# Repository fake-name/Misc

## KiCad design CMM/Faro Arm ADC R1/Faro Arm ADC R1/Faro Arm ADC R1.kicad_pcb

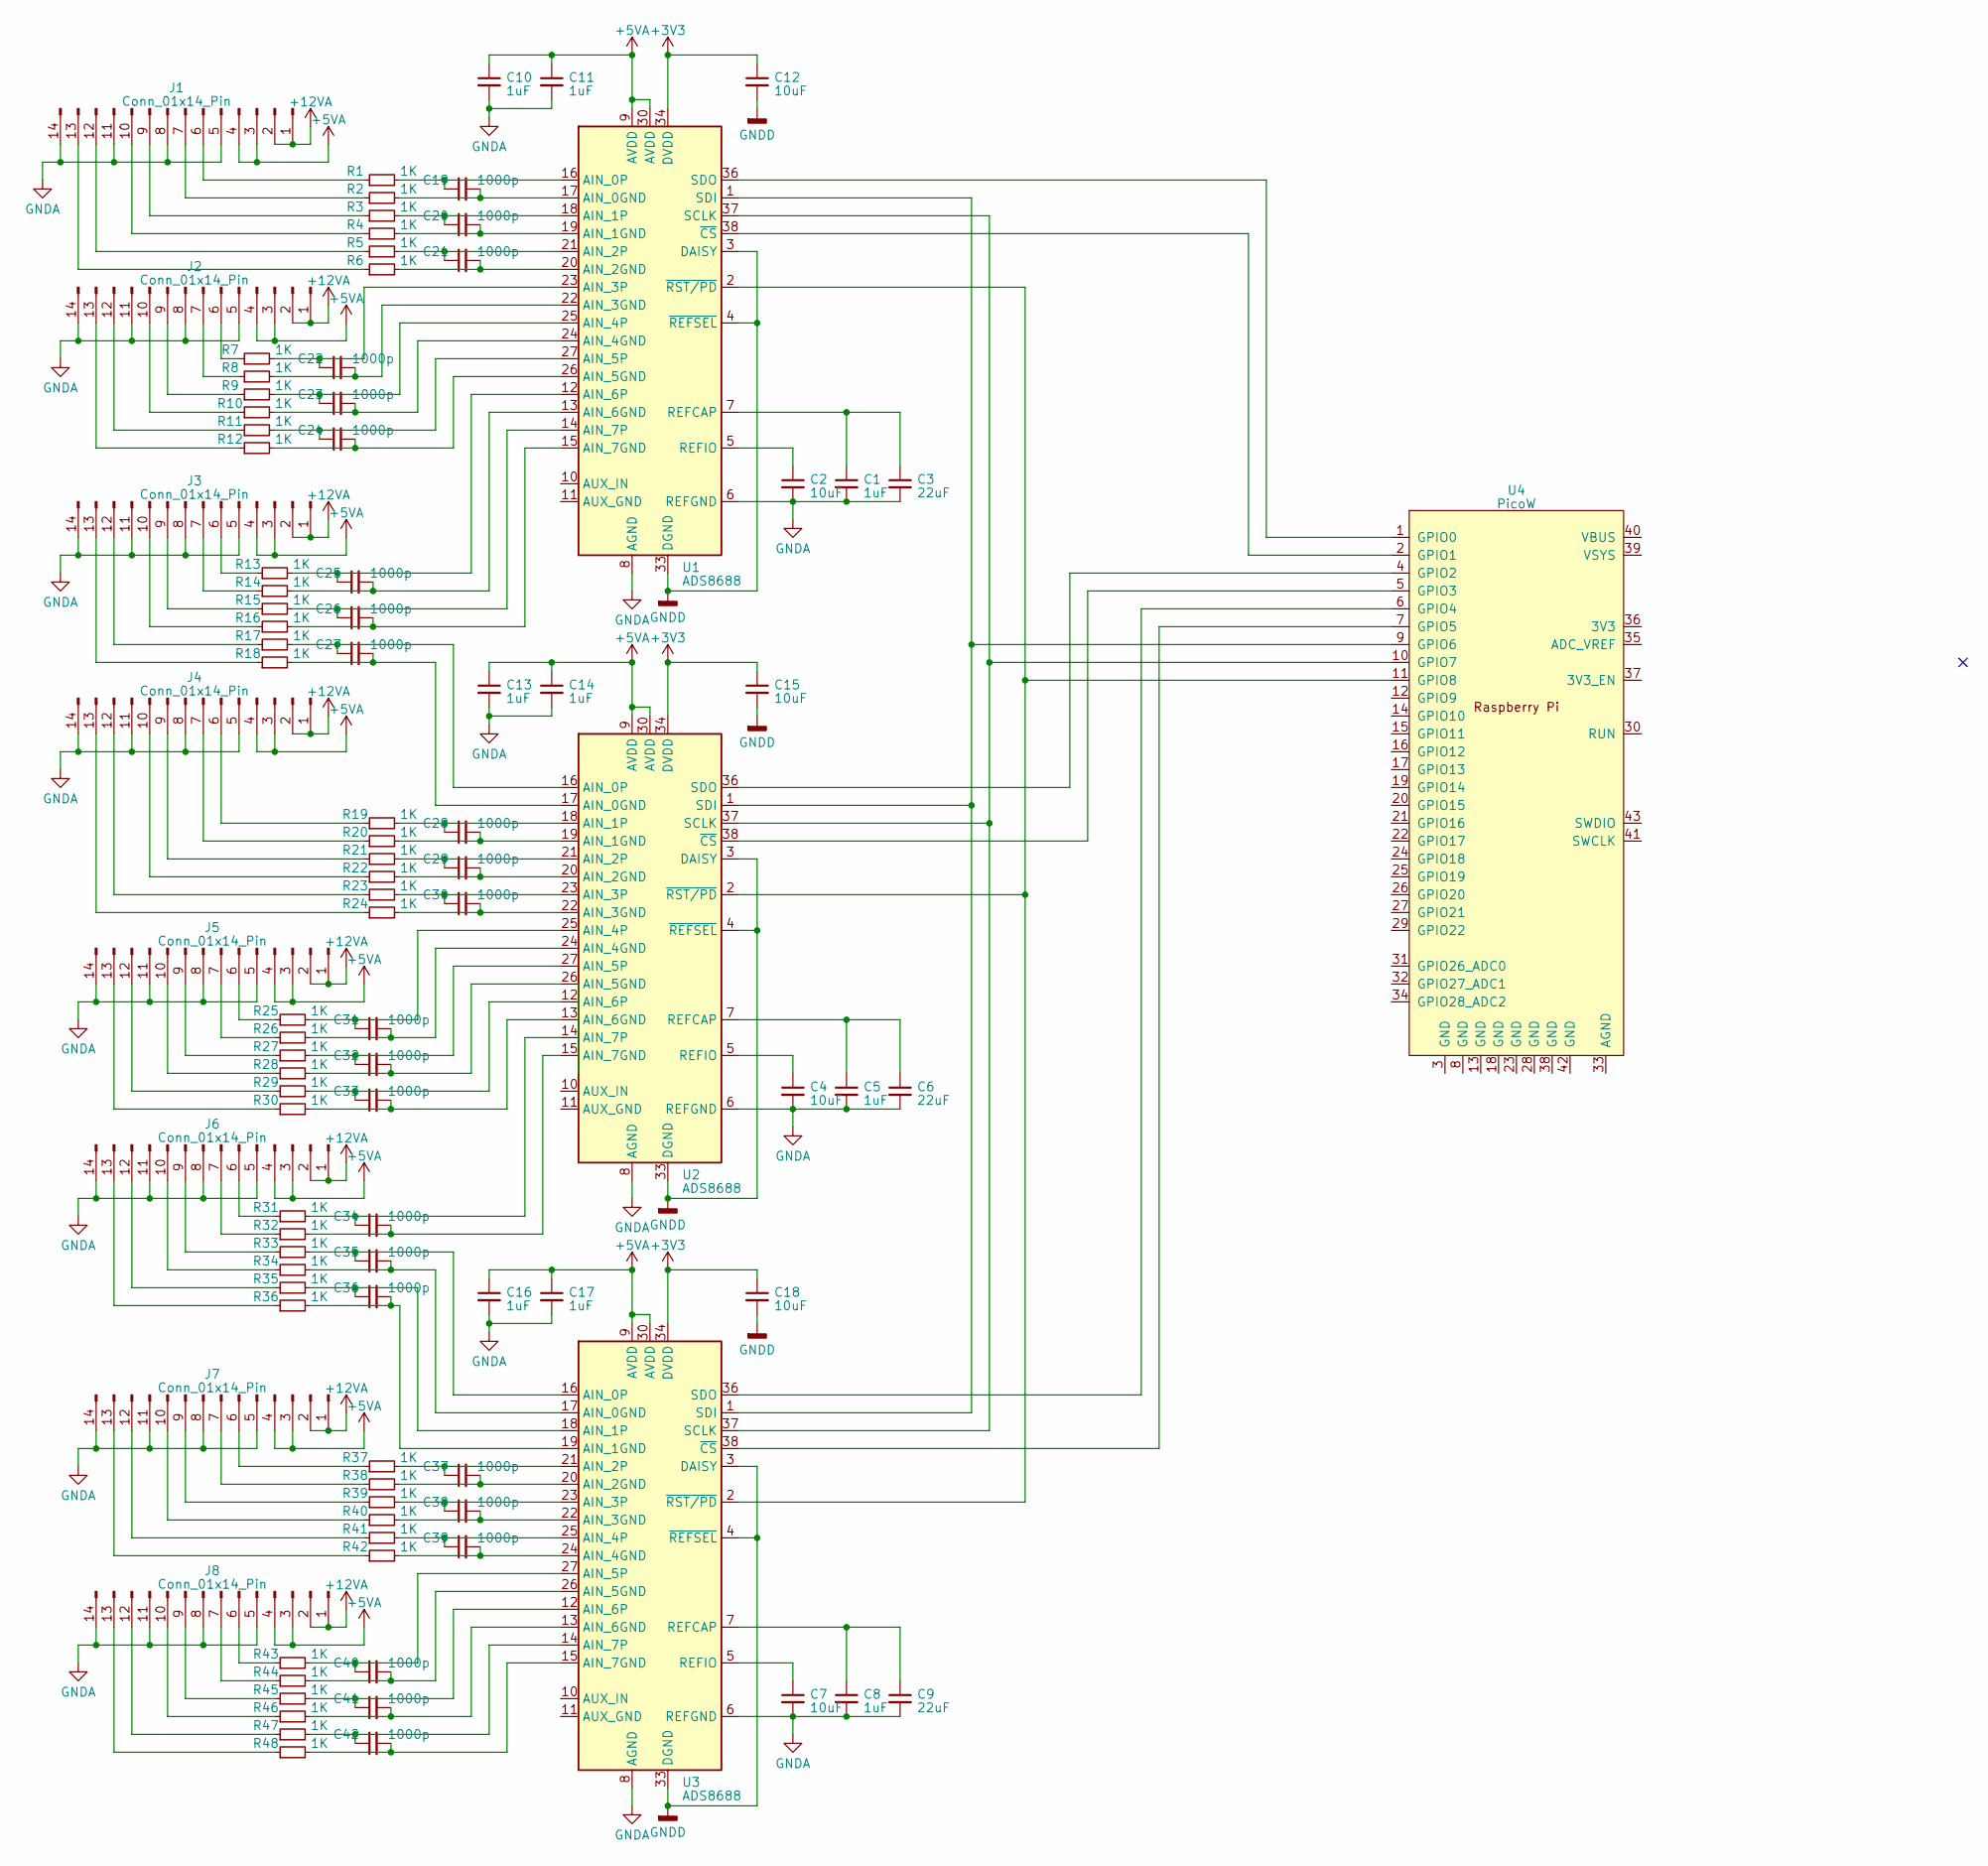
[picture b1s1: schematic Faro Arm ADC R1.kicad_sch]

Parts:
C1, C5, C8, C10, C11, C13, C14, C16, C17: 1uF; C_0603_1608Metric
C2, C4, C7, C12, C15, C18: 10uF; C_0805_2012Metric
C3, C6, C9: 22uF; C_0805_2012Metric
C19, C20, C21, C22, C23, C24, C25, C26, C27, C28, C29, C30, C31, C32, C33, C34, C35, C36, C37, C38, C39, C40, C41, C42: 1000p; C_0603_1608Metric
J1, J2, J3, J4, J5, J6, J7, J8: Conn_01x14_Pin; IDC-Header_2x07_P2.54mm_Vertical
R1, R2, R3, R4, R5, R6, R7, R8, R9, R10, R11, R12, R13, R14, R15, R16, R17, R18, R19, R20, R21, R22, R23, R24, R25, R26, R27, R28, R29, R30, R31, R32, R33, R34, R35, R36, R37, R38, R39, R40, R41, R42, R43, R44, R45, R46, R47, R48: 1K; R_0603_1608Metric
U1, U2, U3: ADS8688; TSSOP-38_4.4x9.7mm_P0.5mm
U4: PicoW; RPi_PicoW_SMD_TH

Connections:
+3V3: C12.1, C15.1, C18.1, U1.34 (DVDD), U2.34 (DVDD), U3.34 (DVDD)
GNDA: C1.2, C2.2, C3.2, C4.2, C5.2, C6.2, C7.2, C8.2, C9.2, C10.2, C11.2, C13.2, C14.2, C16.2, C17.2, J1.5, J1.8, J1.11, J1.14, J2.5, J2.8, J2.11, J2.14, J3.5, J3.8, J3.11, J3.14, J4.5, J4.8, J4.11, J4.14, J5.5, J5.8, J5.11, J5.14, J6.5, J6.8, J6.11, J6.14, J7.5, J7.8, J7.11, J7.14, J8.5, J8.8, J8.11, J8.14, U1.6 (REFGND), U1.8 (AGND), U1.28 (AGND), U1.29 (AGND), U1.31 (AGND), U1.32 (AGND), U2.6 (REFGND), U2.8 (AGND), U2.28 (AGND), U2.29 (AGND), U2.31 (AGND), U2.32 (AGND), U3.6 (REFGND), U3.8 (AGND), U3.28 (AGND), U3.29 (AGND), U3.31 (AGND), U3.32 (AGND)
GNDD: C12.2, C15.2, C18.2, U1.3 (DAISY), U1.4 (~REFSEL), U1.33 (DGND), U2.3 (DAISY), U2.4 (~REFSEL), U2.33 (DGND), U3.3 (DAISY), U3.4 (~REFSEL), U3.33 (DGND)
unnamed: J1.6, R1.1
unnamed: J1.7, R2.1
unnamed: J1.9, R3.1
unnamed: J1.10, R4.1
unnamed: J1.12, R5.1
unnamed: J1.13, R6.1
unnamed: J2.6, R7.1
unnamed: J2.7, R8.1
unnamed: J2.9, R9.1
unnamed: J2.10, R10.1
unnamed: J2.12, R11.1
unnamed: J2.13, R12.1
unnamed: J3.6, R13.1
unnamed: J3.7, R14.1
unnamed: J3.9, R15.1
unnamed: J3.10, R16.1
unnamed: J3.12, R17.1
unnamed: J3.13, R18.1
unnamed: J4.6, R19.1
unnamed: J4.7, R20.1
unnamed: J4.9, R21.1
unnamed: J4.10, R22.1
unnamed: J4.12, R23.1
unnamed: J4.13, R24.1
unnamed: J5.6, R25.1
unnamed: J5.7, R26.1
unnamed: J5.9, R27.1
unnamed: J5.10, R28.1
unnamed: J5.12, R29.1
unnamed: J5.13, R30.1
unnamed: J6.6, R31.1
unnamed: J6.7, R32.1
unnamed: J6.9, R33.1
unnamed: J6.10, R34.1
unnamed: J6.12, R35.1
unnamed: J6.13, R36.1
unnamed: J7.6, R37.1
unnamed: J7.7, R38.1
unnamed: J7.9, R39.1
unnamed: J7.10, R40.1
unnamed: J7.12, R41.1
unnamed: J7.13, R42.1
unnamed: J8.6, R43.1
unnamed: J8.7, R44.1
unnamed: J8.9, R45.1
unnamed: J8.10, R46.1
unnamed: J8.12, R47.1
unnamed: J8.13, R48.1
unnamed: C19.2, R2.2, U1.17 (AIN_0GND)
unnamed: C19.1, R1.2, U1.16 (AIN_0P)
unnamed: C20.2, R4.2, U1.19 (AIN_1GND)
unnamed: C20.1, R3.2, U1.18 (AIN_1P)
unnamed: C21.2, R6.2, U1.20 (AIN_2GND)
unnamed: C21.1, R5.2, U1.21 (AIN_2P)
unnamed: C22.2, R8.2, U1.22 (AIN_3GND)
unnamed: C22.1, R7.2, U1.23 (AIN_3P)
unnamed: C23.2, R10.2, U1.24 (AIN_4GND)
unnamed: C23.1, R9.2, U1.25 (AIN_4P)
unnamed: C24.2, R12.2, U1.26 (AIN_5GND)
unnamed: C24.1, R11.2, U1.27 (AIN_5P)
unnamed: C25.2, R14.2, U1.13 (AIN_6GND)
unnamed: C25.1, R13.2, U1.12 (AIN_6P)
unnamed: C26.2, R16.2, U1.15 (AIN_7GND)
unnamed: C26.1, R15.2, U1.14 (AIN_7P)
unnamed: C1.1, C3.1, U1.7 (REFCAP)
unnamed: C2.1, U1.5 (REFIO)
unnamed: U1.37 (SCLK), U2.37 (SCLK), U3.37 (SCLK), U4.10 (GPIO7)
unnamed: U1.1 (SDI), U2.1 (SDI), U3.1 (SDI), U4.9 (GPIO6)
unnamed: U1.36 (SDO), U4.1 (GPIO0)
unnamed: U1.38 (~CS), U4.2 (GPIO1)
unnamed: U1.2 (~RST/PD), U2.2 (~RST/PD), U3.2 (~RST/PD), U4.11 (GPIO8)
unnamed: C27.2, R18.2, U2.17 (AIN_0GND)
unnamed: C27.1, R17.2, U2.16 (AIN_0P)
unnamed: C28.2, R20.2, U2.19 (AIN_1GND)
unnamed: C28.1, R19.2, U2.18 (AIN_1P)
unnamed: C29.2, R22.2, U2.20 (AIN_2GND)
unnamed: C29.1, R21.2, U2.21 (AIN_2P)
unnamed: C30.2, R24.2, U2.22 (AIN_3GND)
unnamed: C30.1, R23.2, U2.23 (AIN_3P)
unnamed: C31.2, R26.2, U2.24 (AIN_4GND)
unnamed: C31.1, R25.2, U2.25 (AIN_4P)
unnamed: C32.2, R28.2, U2.26 (AIN_5GND)
unnamed: C32.1, R27.2, U2.27 (AIN_5P)
unnamed: C33.2, R30.2, U2.13 (AIN_6GND)
unnamed: C33.1, R29.2, U2.12 (AIN_6P)
unnamed: C34.2, R32.2, U2.15 (AIN_7GND)
unnamed: C34.1, R31.2, U2.14 (AIN_7P)
unnamed: C5.1, C6.1, U2.7 (REFCAP)
unnamed: C4.1, U2.5 (REFIO)
unnamed: U2.36 (SDO), U4.4 (GPIO2)
unnamed: U2.38 (~CS), U4.5 (GPIO3)
unnamed: C35.2, R34.2, U3.17 (AIN_0GND)
unnamed: C35.1, R33.2, U3.16 (AIN_0P)
unnamed: C36.2, R36.2, U3.19 (AIN_1GND)
unnamed: C36.1, R35.2, U3.18 (AIN_1P)
unnamed: C37.2, R38.2, U3.20 (AIN_2GND)
unnamed: C37.1, R37.2, U3.21 (AIN_2P)
unnamed: C38.2, R40.2, U3.22 (AIN_3GND)
unnamed: C38.1, R39.2, U3.23 (AIN_3P)
unnamed: C39.2, R42.2, U3.24 (AIN_4GND)
unnamed: C39.1, R41.2, U3.25 (AIN_4P)
unnamed: C40.2, R44.2, U3.26 (AIN_5GND)
unnamed: C40.1, R43.2, U3.27 (AIN_5P)
unnamed: C41.2, R46.2, U3.13 (AIN_6GND)
unnamed: C41.1, R45.2, U3.12 (AIN_6P)
unnamed: C42.2, R48.2, U3.15 (AIN_7GND)
unnamed: C42.1, R47.2, U3.14 (AIN_7P)
unnamed: C8.1, C9.1, U3.7 (REFCAP)
unnamed: C7.1, U3.5 (REFIO)
unnamed: U3.36 (SDO), U4.6 (GPIO4)
unnamed: U3.38 (~CS), U4.7 (GPIO5)

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
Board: 2 copper layers, 102 parts (0 on the bottom side), 115 nets, no tracks yet.

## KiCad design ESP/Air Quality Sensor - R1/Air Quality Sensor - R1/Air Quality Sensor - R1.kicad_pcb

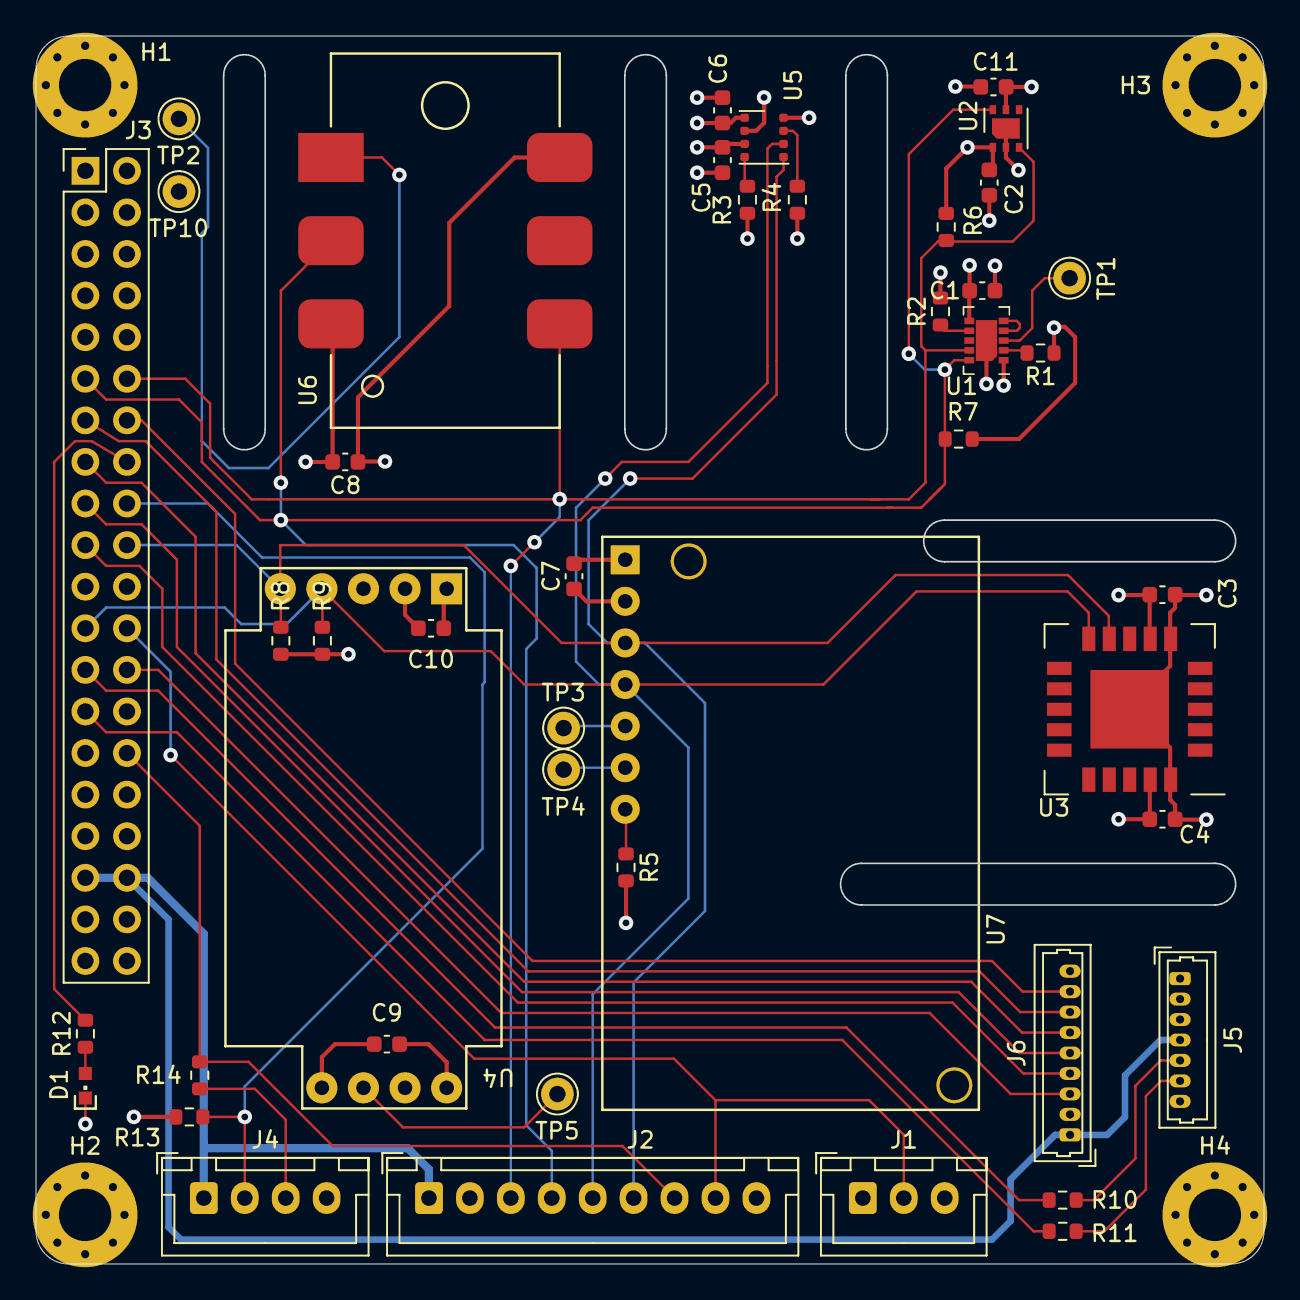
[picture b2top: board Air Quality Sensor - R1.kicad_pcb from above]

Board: 4 copper layers, 75.0 x 75.0 mm, 49 parts (0 on the bottom side), 34 nets.

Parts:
C1, C3, C4, C5, C6, C8, C9, C10, C11: 0.1u; C_0603_1608Metric
C2, C7: 1.0u; C_0603_1608Metric
D1: LED; CHIPLED_0603
H1, H2, H3, H4: MountingHole; MountingHole_3.2mm_M3_Pad_Via
J1: Conn_01x05; JST_XH_B3B-XH-A_1x03_P2.50mm_Vertical
J2: Conn_01x09; JST_XH_B9B-XH-A_1x09_P2.50mm_Vertical
J3: ESP32-DevBoard-Header; PinHeader_2x20_P2.54mm_Vertical
J4: Conn_01x04; JST_XH_B4B-XH-A_1x04_P2.50mm_Vertical
J5: Conn_01x09; Molex_PicoBlade_53047-0710_1x07_P1.25mm_Vertical
J6: Conn_01x08; Molex_PicoBlade_53047-0910_1x09_P1.25mm_Vertical
R1, R3, R4, R5, R6, R7, R8, R9, R10, R11, R13: 4.7K; R_0603_1608Metric
R2: 47K; R_0603_1608Metric
R12, R14: 470R; R_0603_1608Metric
TP1, TP2, TP3, TP4, TP5, TP10: TestPoint_Small; Pin_D1.0mm_L10.0mm
U1: CCS811; AMS_LGA-10-1EP_2.7x4mm_P0.6mm
U2: SGP40; Sensirion_DFN-6-1EP_2.44x2.44mm_P0.8mm
U3: SCD4X; Sensirion_SCD4X_QFN-20_EP_10.1x10.1_Pitch1.25mm
U4: Sensair_Sunrise_006-0-0007
U5: BME680; Bosch_LGA-8_3x3mm_P0.8mm_ClockwisePinNumbering
U6: MICS-VZ-89TE‎; Telaire_MICS-VZ-89TE‎
U7: SCD30; Sensiron_SCD30_Module

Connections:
+3V3: C1.1, C2.1, C3.1, C4.1, C5.1, C6.1, C7.1, C8.1, C9.1, C10.1, C11.1, J1.1, J2.2, J3.3 (3V3), J3.4 (3V3), J3.33 (3V3), J3.34 (3V3), J6.2, R1.1, R3.1, R4.1, R6.2, R7.2, R8.2, R9.2, R13.2, U1.6 (VDD), U2.1 (VDD), U2.5 (VDDH), U3.7 (VDD), U3.19 (VDDH), U4.2 (VBB), U4.3 (VDDIO), U4.9 (EN), U5.6 (VDDIO), U5.8 (VDD), U6.6 (3.3V), U7.1 (VDD)
+5V: J2.1, J3.35 (5V0), J3.36 (5V0), J4.1, J5.4, J6.1
/SENS/SCL_1: J2.6, J3.20 (IO22), R8.1, U3.9 (SCL), U4.5 (TxD/SCL), U5.4 (SCK), U7.3 (TX/SCL)
/SENS/SCL_2: J2.4, J3.11 (IO32), R7.1, U1.10 (SCL), U2.6 (SCL), U6.2 (SCL)
/SENS/SDA_1: J2.5, J3.23 (IO21), R9.1, U3.10 (SDA), U4.4 (RxD/SDA), U5.3 (SDI), U7.4 (RX/SDA)
/SENS/SDA_2: J2.3, J3.12 (IO33), R6.1, U1.9 (SDA), U2.3 (SDA), U6.4 (SDA)
GND: C1.2, C2.2, C3.2, C4.2, C5.2, C6.2, C7.2, C8.2, C9.2, C10.2, C11.2, D1.1 (K), J1.3, J2.9, J3.1 (GND), J3.2 (GND), J3.5 (GND), J3.6 (GND), J3.31 (GND), J3.32 (GND), J3.39 (GND), J3.40 (GND), J4.4, J5.3, J6.9, R2.2, R5.2, TP10.1, U1.1 (ADDR), U1.11 (GND), U2.2 (VSS), U2.7 (EP1), U3.6 (GND), U3.20 (GND), U3.21 (EP), U4.1 (GND), U4.6 (COMSEL), U5.1 (GND), U5.7 (GND), U6.3 (GND), U7.2 (GND)
unnamed: D1.2 (A), R12.1
unnamed: J1.2, J2.8, J3.24 (IO19)
unnamed: J2.7, J3.30 (IO15), R14.2
unnamed: J3.13 (IO25), J6.7
unnamed: J3.14 (IO26), J6.8
unnamed: J3.15 (IO27), J6.6
unnamed: J3.16 (IO14), R12.2
unnamed: J3.17 (IO12), J6.5
unnamed: J3.18 (IO13), J4.2, R13.1
unnamed: J3.19 (IO23), J6.4
unnamed: J3.25 (IO18), R10.2
unnamed: J3.26 (IO5), J6.3
unnamed: J3.27 (IO4), R11.2
unnamed: J4.3, R14.1
unnamed: J5.5, R10.1
unnamed: J5.6, R11.1
unnamed: R1.2, U1.2 (~RESET)
unnamed: R2.1, U1.7 (~WAKE)
unnamed: R3.2, U5.5 (SDO)
unnamed: R4.2, U5.2 (CSB)
unnamed: R5.1, U7.7 (SEL)
unnamed: TP1.1, U1.3 (~INT)
unnamed: TP2.1, U6.1 (PWM)
unnamed: TP3.1, U7.5 (RDY)
unnamed: TP4.1, U7.6 (PWM)
unnamed: TP5.1, U4.7 (nRDY)
unnamed: U1.4 (PWM), U1.5 (Sense)

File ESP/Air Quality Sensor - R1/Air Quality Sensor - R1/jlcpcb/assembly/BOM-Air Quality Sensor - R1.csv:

Comment,Designator,Footprint,LCSC
470R,R14,R_0603_1608Metric,
4.7K,R13,R_0603_1608Metric,
470R,R12,R_0603_1608Metric,
4.7K,R9,R_0603_1608Metric,
4.7K,R8,R_0603_1608Metric,
4.7K,R7,R_0603_1608Metric,
4.7K,R6,R_0603_1608Metric,
4.7K,R5,R_0603_1608Metric,
0.1u,C10,C_0603_1608Metric,
0.1u,C9,C_0603_1608Metric,
0.1u,C8,C_0603_1608Metric,
1.0u,C7,C_0603_1608Metric,
MountingHole,H4,MountingHole_3.2mm_M3_Pad_Via,
MountingHole,H3,MountingHole_3.2mm_M3_Pad_Via,
MountingHole,H2,MountingHole_3.2mm_M3_Pad_Via,
MountingHole,H1,MountingHole_3.2mm_M3_Pad_Via,
ESP32-DevBoard-Header,J3,PinHeader_2x20_P2.54mm_Vertical,
0.1u,C3,C_0603_1608Metric,
Conn_01x04,J4,JST_XH_B4B-XH-A_1x04_P2.50mm_Vertical,
1.0u,C2,C_0603_1608Metric,
0.1u,C11,C_0603_1608Metric,
0.1u,C1,C_0603_1608Metric,
SGP40,U2,Sensirion_DFN-6-1EP_2.44x2.44mm_P0.8mm,
Conn_01x09,J2,JST_XH_B9B-XH-A_1x09_P2.50mm_Vertical,
BME680,U5,Bosch_LGA-8_3x3mm_P0.8mm_ClockwisePinNumbering,
SCD30,U7,Sensiron_SCD30_Module,
MICS-VZ-89TE‎,U6,Telaire_MICS-VZ-89TE‎,
4.7K,R4,R_0603_1608Metric,
4.7K,R3,R_0603_1608Metric,
CCS811,U1,AMS_LGA-10-1EP_2.7x4mm_P0.6mm,
4.7K,R1,R_0603_1608Metric,
SCD4X,U3,Sensirion_SCD4X_QFN-20_EP_10.1x10.1_Pitch1.25mm,
Conn_01x05,J1,JST_XH_B3B-XH-A_1x03_P2.50mm_Vertical,
Sensair_Sunrise_006-0-0007,U4,Sensair_Sunrise_006-0-0007,
0.1u,C5,C_0603_1608Metric,
0.1u,C6,C_0603_1608Metric,
TestPoint_Small,TP1,Pin_D1.0mm_L10.0mm,
LED,D1,CHIPLED_0603,
47K,R2,R_0603_1608Metric,
0.1u,C4,C_0603_1608Metric,
TestPoint_Small,TP10,Pin_D1.0mm_L10.0mm,
TestPoint_Small,TP5,Pin_D1.0mm_L10.0mm,
TestPoint_Small,TP4,Pin_D1.0mm_L10.0mm,
TestPoint_Small,TP3,Pin_D1.0mm_L10.0mm,
TestPoint_Small,TP2,Pin_D1.0mm_L10.0mm,
4.7K,R11,R_0603_1608Metric,
4.7K,R10,R_0603_1608Metric,
Conn_01x09,J5,Molex_PicoBlade_53047-0710_1x07_P1.25mm_Vertical,
Conn_01x08,J6,Molex_PicoBlade_53047-0910_1x09_P1.25mm_Vertical,

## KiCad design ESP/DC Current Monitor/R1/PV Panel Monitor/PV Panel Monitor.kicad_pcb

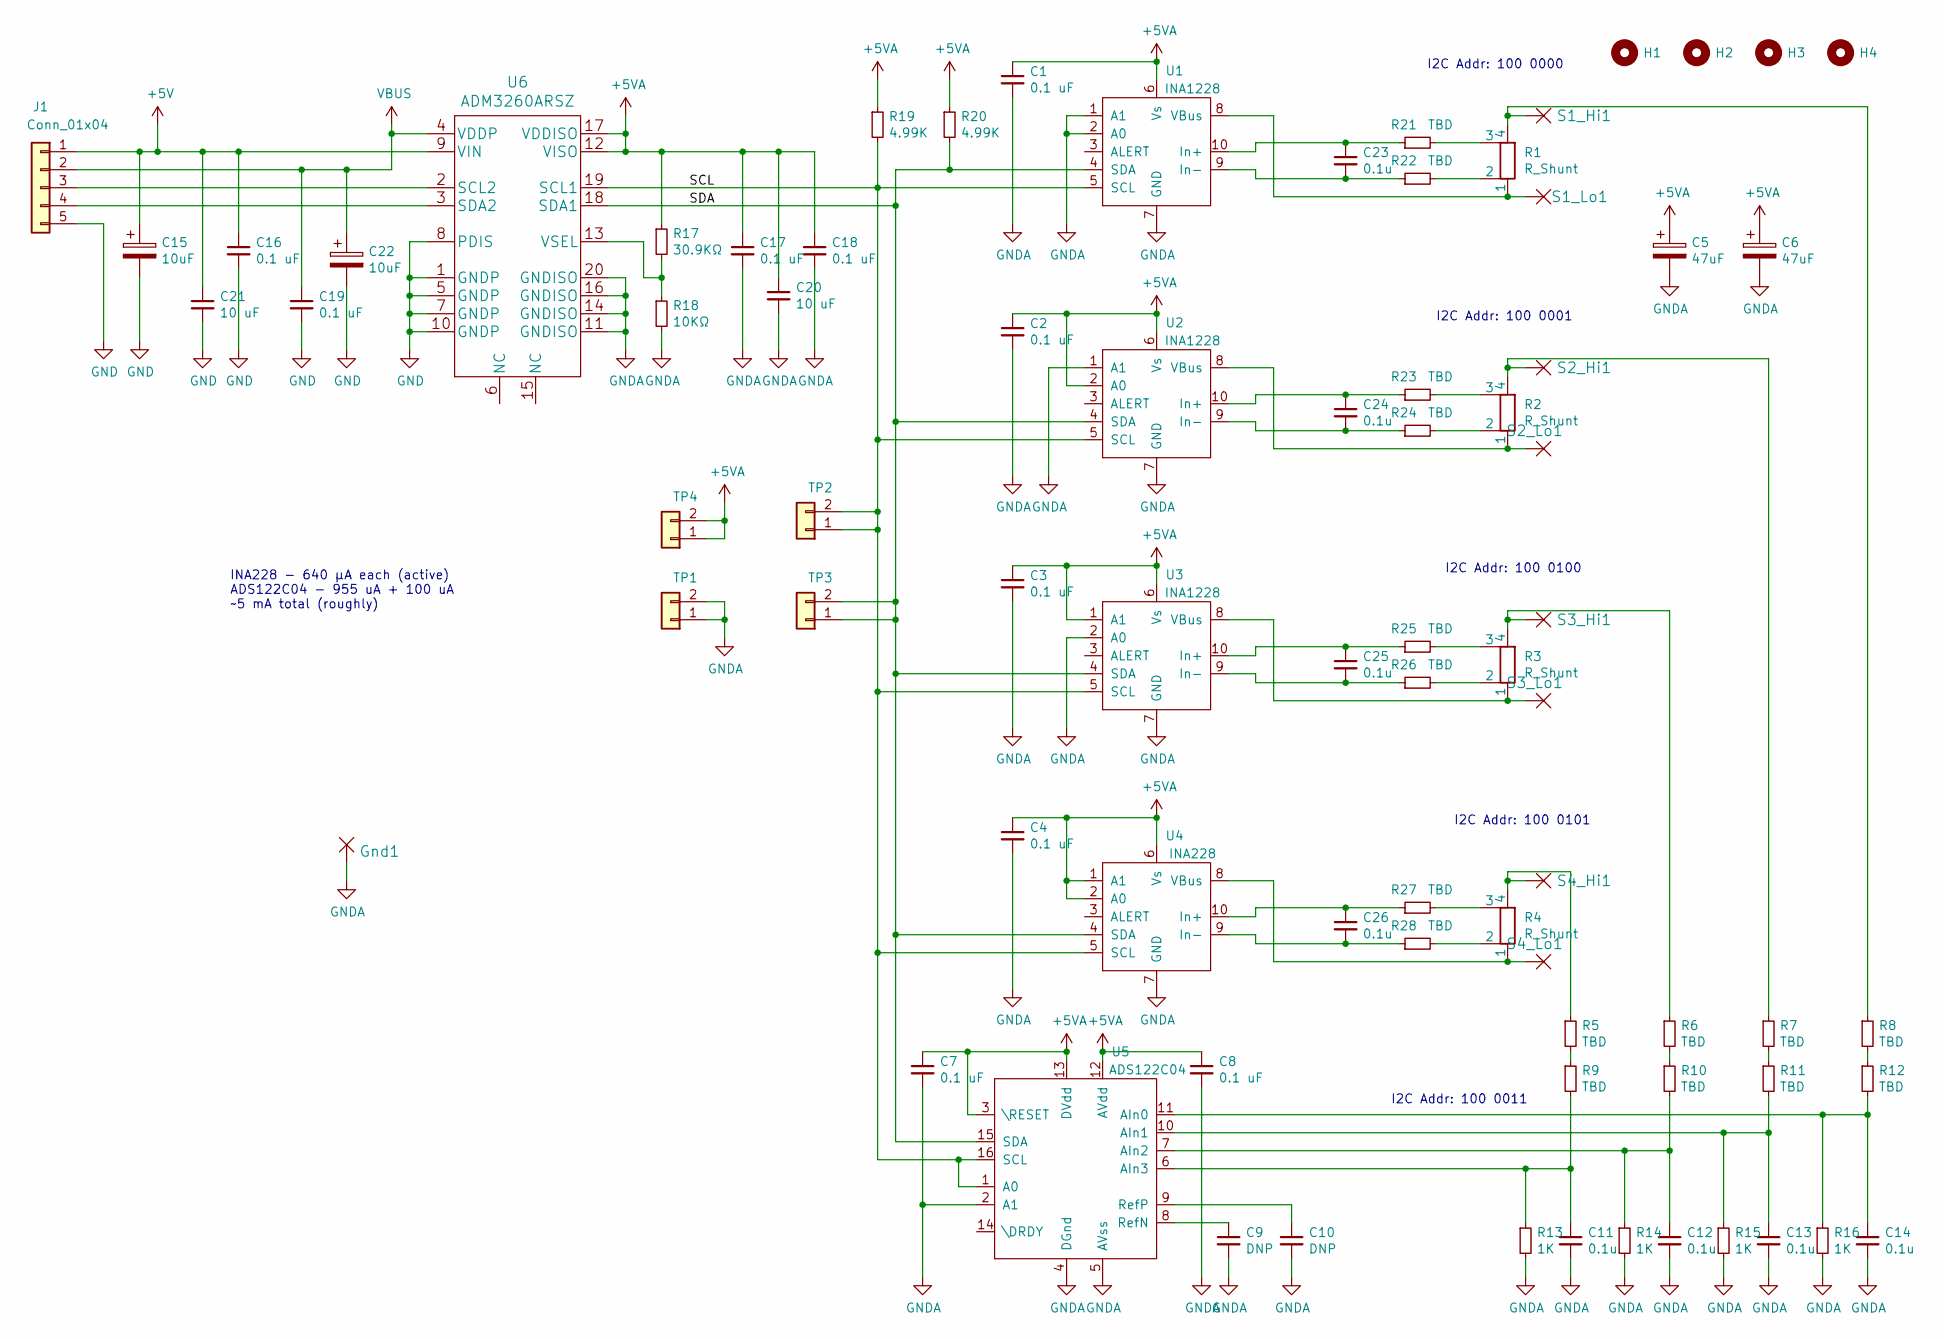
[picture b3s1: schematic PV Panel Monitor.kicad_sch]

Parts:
C1, C2, C3, C4, C7, C8, C16, C17, C18, C19: 0.1 uF; C_0603_1608Metric
C5, C6: 47uF; CP_Radial_D6.3mm_P2.50mm
C9, C10: DNP; C_0603_1608Metric
C11, C12, C13, C14, C23, C24, C25, C26: 0.1u; C_0603_1608Metric
C15, C22: 10uF; CP_Radial_D6.3mm_P2.50mm
C20, C21: 10 uF; C_1206_3216Metric
Gnd1: MountingHole_3mm_Pad_Via
H1, H2, H3, H4: MountingHole; MountingHole_3mm_Pad_Via
J1: Conn_01x04; JST_XH_B5B-XH-A_1x05_P2.50mm_Vertical
R1, R2, R3, R4: R_Shunt; R_Shunt_Vishay_WSKW0612
R5, R6, R7, R8, R9, R10, R11, R12, R21, R22, R23, R24, R25, R26, R27, R28: TBD; R_0603_1608Metric
R13, R14, R15, R16: 1K; R_0603_1608Metric
R17: 30.9KΩ; R_0603_1608Metric
R18: 10KΩ; R_0603_1608Metric
R19, R20: 4.99K; R_0603_1608Metric
S1_Hi1, S1_Lo1, S2_Hi1, S2_Lo1, S3_Hi1, S3_Lo1, S4_Hi1, S4_Lo1: MountingHole_3mm_Pad_Via
TP1, TP2, TP3, TP4: Conn_01x02; PinHeader_1x02_P2.54mm_Vertical
U1, U2, U3: INA1228; MSOP-10_3x3mm_P0.5mm
U4: INA228; MSOP-10_3x3mm_P0.5mm
U5: ADS122C04; TSSOP-16_4.4x5mm_P0.65mm
U6: ADM3260ARSZ; SSOP-20_5.3x7.2mm_P0.65mm

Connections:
+5V: C15.1, C16.1, C21.1, J1.1, U6.9 (VIN)
+5VA: C1.1, C2.1, C3.1, C4.1, C5.1, C6.1, C7.1, C8.1, C17.1, C18.1, C20.1, R17.1, R19.1, R20.1, TP4.1, TP4.2, U1.6 (Vs), U2.2 (A0), U2.6 (Vs), U3.1 (A1), U3.6 (Vs), U4.1 (A1), U4.2 (A0), U4.6 (Vs), U5.3 (\RESET), U5.12 (AVdd), U5.13 (DVdd), U6.12 (VISO), U6.17 (VDDISO)
/SCL: R19.2, TP2.1, TP2.2, U1.5 (SCL), U2.5 (SCL), U3.5 (SCL), U4.5 (SCL), U5.1 (A0), U5.16 (SCL), U6.19 (SCL1)
/SDA: R20.2, TP3.1, TP3.2, U1.4 (SDA), U2.4 (SDA), U3.4 (SDA), U4.4 (SDA), U5.15 (SDA), U6.18 (SDA1)
GND: C15.2, C16.2, C19.2, C21.2, C22.2, J1.5, U6.1 (GNDP), U6.5 (GNDP), U6.7 (GNDP), U6.8 (PDIS), U6.10 (GNDP)
GNDA: C1.2, C2.2, C3.2, C4.2, C5.2, C6.2, C7.2, C8.2, C9.2, C10.2, C11.2, C12.2, C13.2, C14.2, C17.2, C18.2, C20.2, Gnd1.1, R13.2, R14.2, R15.2, R16.2, R18.2, TP1.1, TP1.2, U1.1 (A1), U1.2 (A0), U1.7 (GND), U2.1 (A1), U2.7 (GND), U3.2 (A0), U3.7 (GND), U4.7 (GND), U5.2 (A1), U5.4 (DGnd), U5.5 (AVss), U6.11 (GNDISO), U6.14 (GNDISO), U6.16 (GNDISO), U6.20 (GNDISO)
unnamed: C9.1, U5.8 (RefN)
unnamed: C11.1, R9.2, R13.1, U5.6 (AIn3)
unnamed: C12.1, R10.2, R14.1, U5.7 (AIn2)
unnamed: C13.1, R11.2, R15.1, U5.10 (AIn1)
unnamed: C14.1, R12.2, R16.1, U5.11 (AIn0)
unnamed: J1.3, U6.2 (SCL2)
unnamed: J1.4, U6.3 (SDA2)
unnamed: R1.1, S1_Lo1.1, U1.8 (VBus)
unnamed: R1.2, R22.2
unnamed: R1.3, R21.2
unnamed: R1.4, R8.1, S1_Hi1.1
unnamed: R2.1, S2_Lo1.1, U2.8 (VBus)
unnamed: R2.2, R24.2
unnamed: R2.3, R23.2
unnamed: R2.4, R7.1, S2_Hi1.1
unnamed: R3.2, R26.2
unnamed: R3.3, R25.2
unnamed: R3.4, R6.1, S3_Hi1.1
unnamed: R4.1, S4_Lo1.1, U4.8 (VBus)
unnamed: R4.2, R28.2
unnamed: R4.3, R27.2
unnamed: R4.4, R5.1, S4_Hi1.1
unnamed: R5.2, R9.1
unnamed: R6.2, R10.1
unnamed: R7.2, R11.1
unnamed: R8.2, R12.1
unnamed: R17.2, R18.1, U6.13 (VSEL)
unnamed: C23.2, R22.1, U1.9 (In-)
unnamed: C23.1, R21.1, U1.10 (In+)
unnamed: C24.2, R24.1, U2.9 (In-)
unnamed: C24.1, R23.1, U2.10 (In+)
unnamed: R3.1, S3_Lo1.1, U3.8 (VBus)
unnamed: C25.2, R26.1, U3.9 (In-)
unnamed: C25.1, R25.1, U3.10 (In+)
unnamed: C26.2, R28.1, U4.9 (In-)
unnamed: C26.1, R27.1, U4.10 (In+)
unnamed: C10.1, U5.9 (RefP)
VBUS: C19.1, C22.1, J1.2, U6.4 (VDDP)

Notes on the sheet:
I2C Addr: 100 0101
I2C Addr: 100 0000
I2C Addr: 100 0011
I2C Addr: 100 0001
INA228 - 640 µA each (active) ADS122C04 - 955 uA + 100 uA ~5 mA total (roughly)
I2C Addr: 100 0100

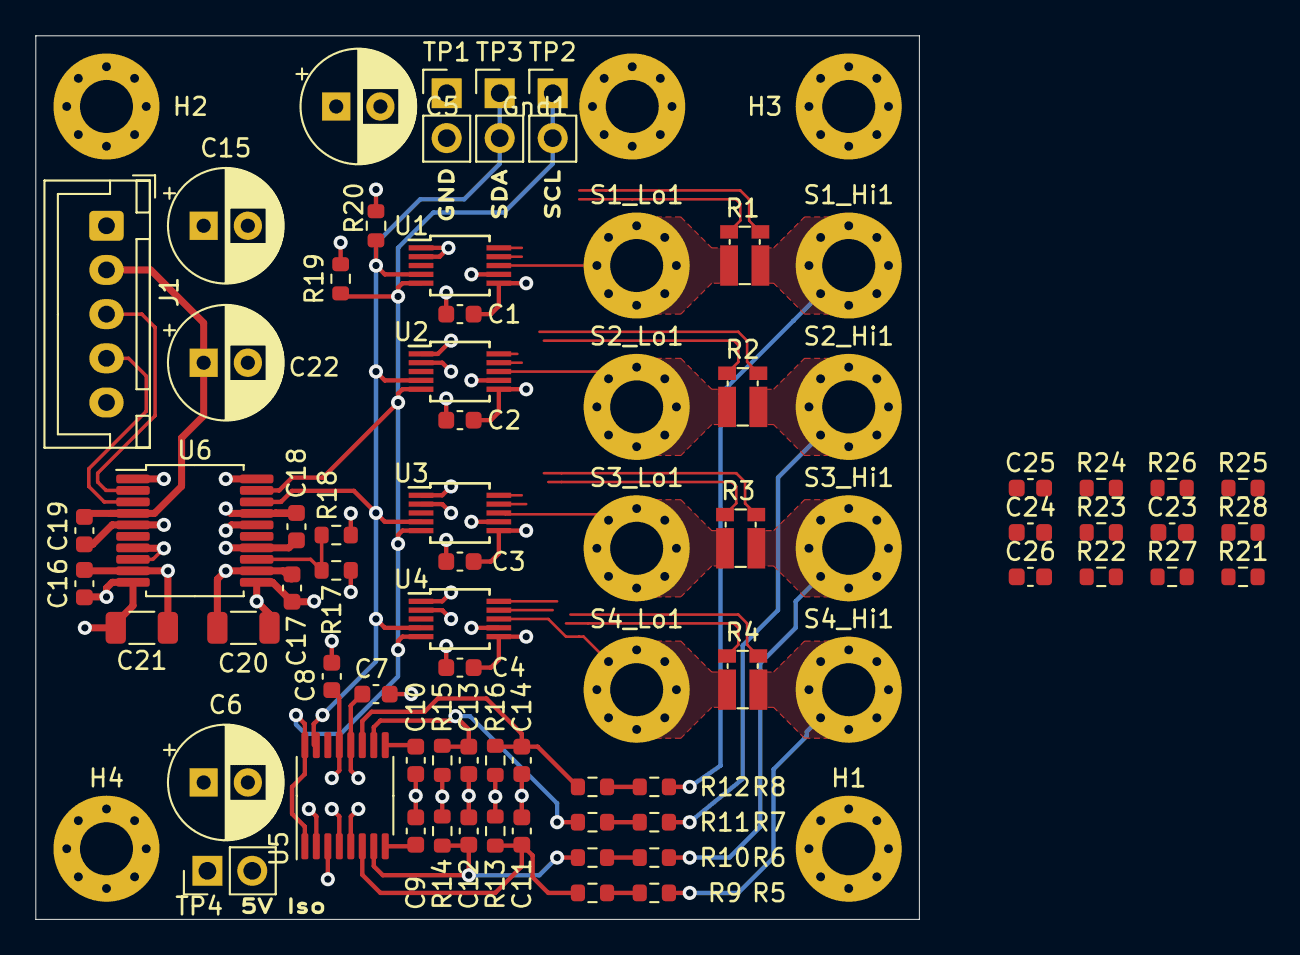
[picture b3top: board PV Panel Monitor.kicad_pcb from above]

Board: 4 copper layers, 50.0 x 50.0 mm, 78 parts (0 on the bottom side), 44 nets.

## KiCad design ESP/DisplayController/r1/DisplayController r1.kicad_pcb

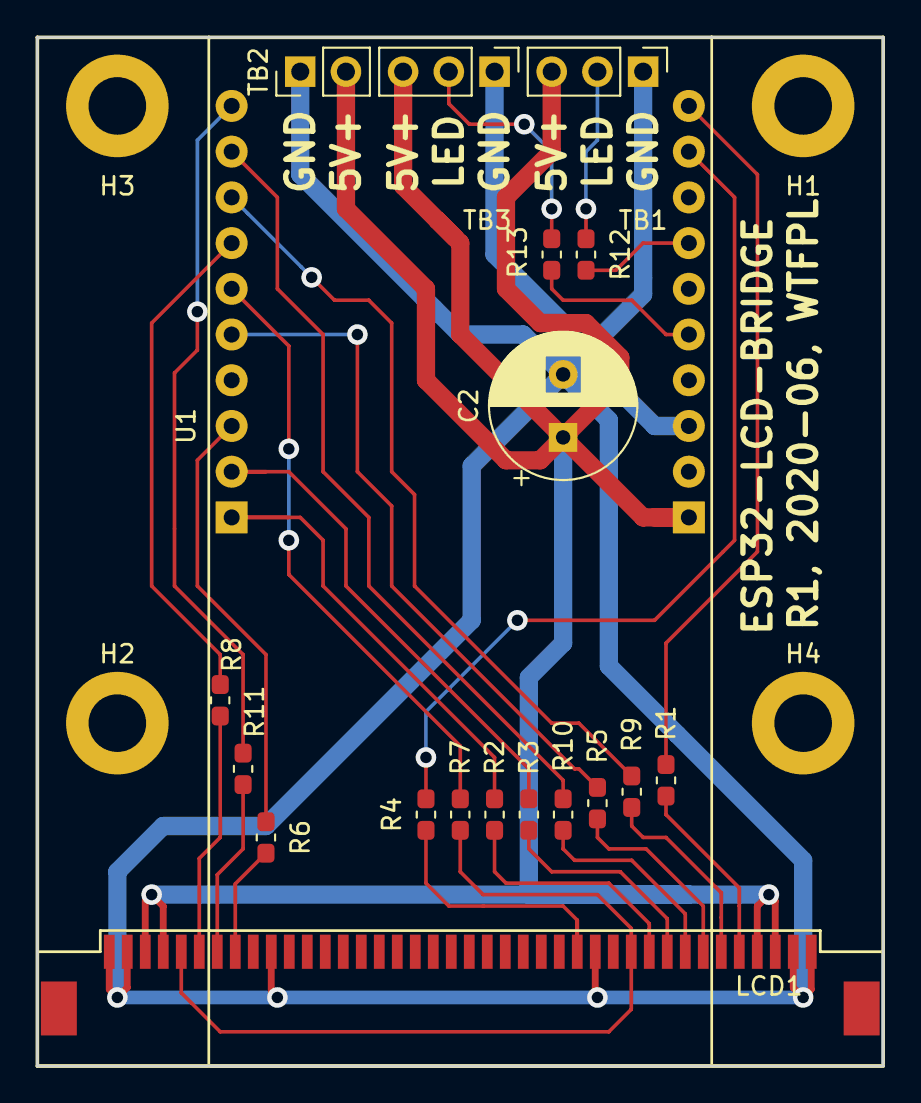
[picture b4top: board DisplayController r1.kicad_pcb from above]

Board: 2 copper layers, 47.0 x 57.1 mm, 23 parts (0 on the bottom side), 28 nets.

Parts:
C2: 47uF_Pol; CP_Radial_D8.0mm_P3.50mm
H1, H2, H3, H4: MountingHole; MountingHole_3.2mm_M3_ISO7380_Pad
LCD1: ER-TFT101-1; FPC_40
R1, R2, R3, R4, R5, R6, R7, R8, R9, R10, R11, R12, R13: 1.00kΩ; R_0603_1608Metric_Pad1.05x0.95mm_HandSolder
TB1, TB3: CONN_1x3; PinHeader_1x03_P2.54mm_Vertical
TB2: Conn_01x02; PinHeader_1x02_P2.54mm_Vertical
U1: ESP32-POE

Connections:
+5V: C2.1, LCD1.3, LCD1.4, LCD1.37, LCD1.38, TB1.3, TB2.2, TB3.3, U1.1
/BL_PWM: LCD1.14, R4.1
/CP_INT: LCD1.33, R6.1
/CTP_SCL: LCD1.35, R8.1
/CTP_SDA: LCD1.34, R11.1
/INT: LCD1.10, R2.1
/I_BL_PWM: R4.2, U1.9
/I_CP_INT: R6.2, U1.13
/I_CTP_SCL: R8.2, U1.17
/I_CTP_SDA: R11.2, U1.20
/I_INT: R2.2, U1.11
/I_RESET: R7.2, U1.16
/I_SCK: R10.2, U1.19
/I_SCS: R1.2, U1.10
/I_SDI: R5.2, U1.15
/I_SDO: R9.2, U1.18
/I_WAIT: R3.2, U1.12
/RESET: LCD1.11, LCD1.36, R7.1
/SCK: LCD1.8, R10.1
/SCS: LCD1.5, R1.1
/SDI: LCD1.7, R5.1
/SDO: LCD1.6, R9.1
/WAIT: LCD1.9, R3.1
GND: C2.2, LCD1.1, LCD1.2, LCD1.13, LCD1.31, LCD1.39, LCD1.40, TB1.1, TB2.1, TB3.1, U1.3
unnamed: R12.1, TB1.2
unnamed: R12.2, U1.7
unnamed: R13.1, TB3.2
unnamed: R13.2, U1.5

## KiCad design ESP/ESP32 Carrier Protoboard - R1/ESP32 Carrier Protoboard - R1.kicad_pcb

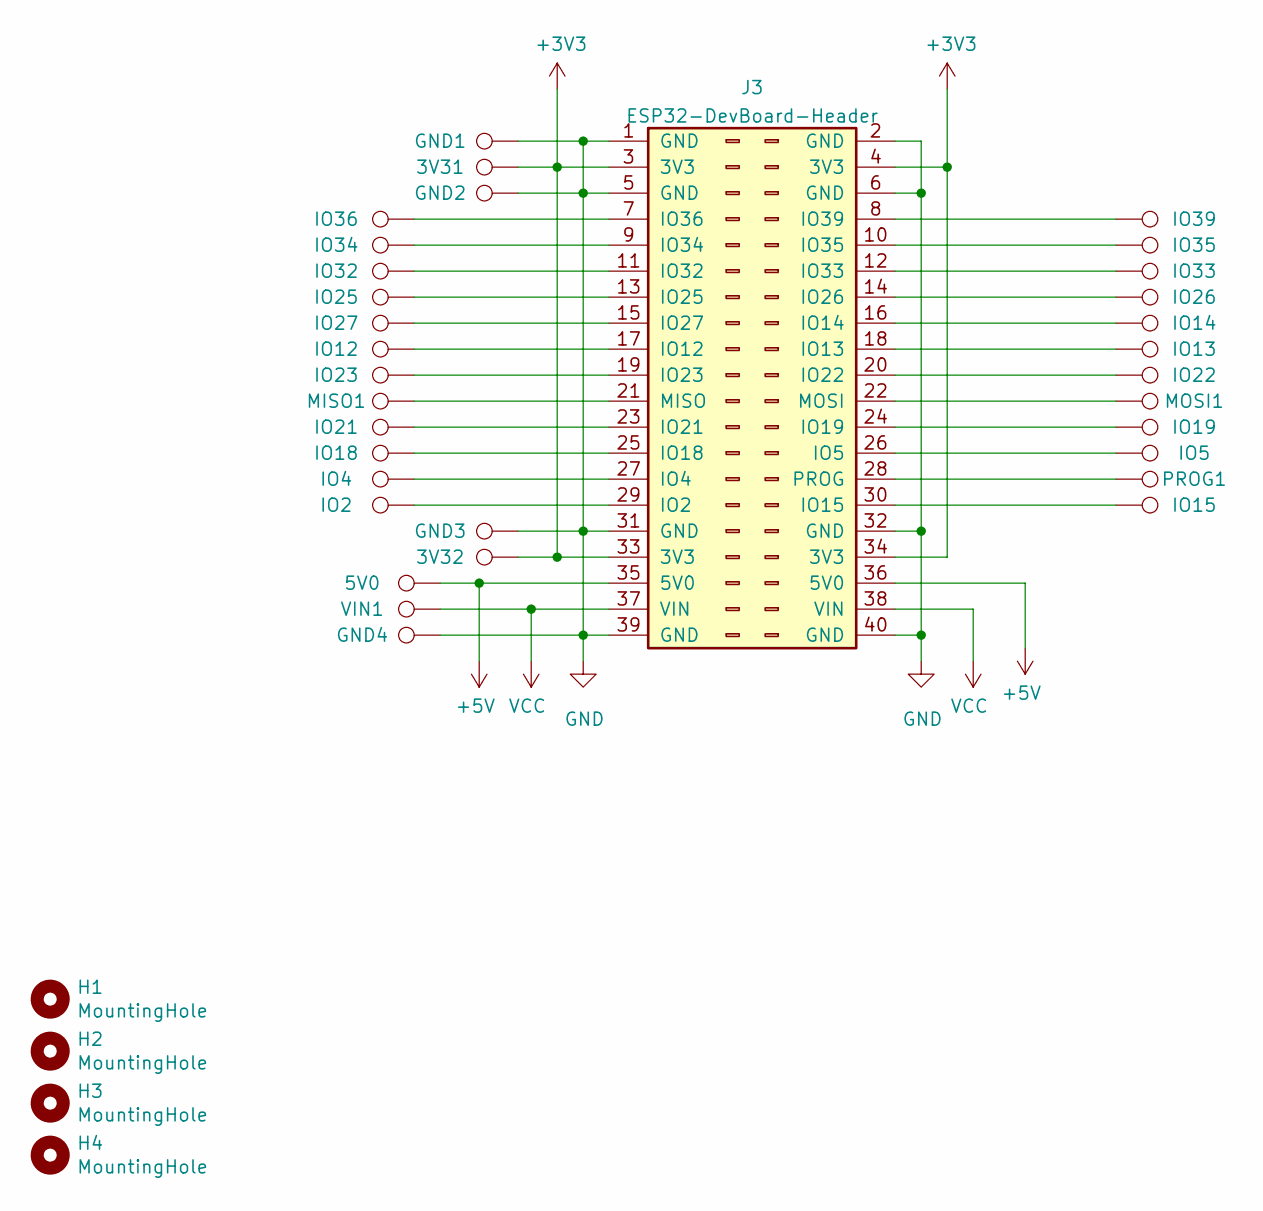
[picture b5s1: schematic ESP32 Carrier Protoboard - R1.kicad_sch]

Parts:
3V31, 3V32, 5V0: TestPoint; TestPoint_Bridge_Pitch2.54mm_Drill1.0mm
GND1, GND2, GND3, GND4: TestPoint; TestPoint_Bridge_Pitch2.54mm_Drill1.0mm
H1, H2, H3, H4: MountingHole; MountingHole_2.5mm_Pad_Via
IO2, IO4, IO5, IO12, IO13, IO14, IO15, IO18, IO19, IO21, IO22, IO23, IO25, IO26, IO27, IO32, IO33, IO34, IO35, IO36, IO39: TestPoint; TestPoint_Bridge_Pitch2.54mm_Drill1.0mm
J3: ESP32-DevBoard-Header; PinHeader_2x20_P2.54mm_Vertical
MISO1: TestPoint; TestPoint_Bridge_Pitch2.54mm_Drill1.0mm
MOSI1: TestPoint; TestPoint_Bridge_Pitch2.54mm_Drill1.0mm
PROG1: TestPoint; TestPoint_Bridge_Pitch2.54mm_Drill1.0mm
VIN1: TestPoint; TestPoint_Bridge_Pitch2.54mm_Drill1.0mm

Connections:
+3V3: 3V31.1, 3V32.1, J3.3 (3V3), J3.4 (3V3), J3.33 (3V3), J3.34 (3V3)
+5V: 5V0.1, J3.35 (5V0), J3.36 (5V0)
GND: GND1.1, GND2.1, GND3.1, GND4.1, J3.1 (GND), J3.2 (GND), J3.5 (GND), J3.6 (GND), J3.31 (GND), J3.32 (GND), J3.39 (GND), J3.40 (GND)
unnamed: IO2.1, J3.29 (IO2)
unnamed: IO4.1, J3.27 (IO4)
unnamed: IO5.1, J3.26 (IO5)
unnamed: IO12.1, J3.17 (IO12)
unnamed: IO13.1, J3.18 (IO13)
unnamed: IO14.1, J3.16 (IO14)
unnamed: IO15.1, J3.30 (IO15)
unnamed: IO18.1, J3.25 (IO18)
unnamed: IO19.1, J3.24 (IO19)
unnamed: IO21.1, J3.23 (IO21)
unnamed: IO22.1, J3.20 (IO22)
unnamed: IO23.1, J3.19 (IO23)
unnamed: IO25.1, J3.13 (IO25)
unnamed: IO26.1, J3.14 (IO26)
unnamed: IO27.1, J3.15 (IO27)
unnamed: IO32.1, J3.11 (IO32)
unnamed: IO33.1, J3.12 (IO33)
unnamed: IO34.1, J3.9 (IO34)
unnamed: IO35.1, J3.10 (IO35)
unnamed: IO36.1, J3.7 (IO36)
unnamed: IO39.1, J3.8 (IO39)
unnamed: J3.21 (MISO), MISO1.1
unnamed: J3.22 (MOSI), MOSI1.1
unnamed: J3.28 (PROG), PROG1.1
VCC: J3.37 (VIN), J3.38 (VIN), VIN1.1
